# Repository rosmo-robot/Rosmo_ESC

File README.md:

# Rosmo ESC

Design for [Rosmo](https://rosmo.io) ESC - in M5Stack format.

[Schematic (PDF)](./Rosmo_ESC.pdf)

Top:

Bottom:

## Features

* Dual brushless motor ESC in M5-Stack module format
* Drives 2x 3-phase BLDC motors with up to 40V and 5A (cooling needed - to be tested)
* 2x SPI sensors supported, such as MA732, MA730, AS5048A, AS5047, etc...
* Control inputs via SPI, I2C    (and GPIO:question:)
* Grove port for I2C input/output

## Status

:warning: In development, prototype boards on order.

At the moment, schematic is complete and board has been routed. The BOM is complete but my have to change due to component availability.

**Do not use this for anything yet!**

## Pinout

Prototype pinout, based on STM32G491MET6, which is probably not the final MCU for this design, but a suitable (if maybe overpowered and therefore expensive) one that was available in the current semiconductor shortage. This MCU is 12x12mm LQFP-80, which is more than enough pins.

Functionality supported by this pinout:

* 2x 3-phase BLDC motor control with 6 PWM (6 outputs on TIM1 and 6 on TIM8, in CHx/CHxN configuration)
* 2x nSLEEP outputs (GPIO)
* 2x nFAULT inputs (interrupt GPIO)
* 2x 3-phase low-side current sensing (6 single-ended inputs on ADC1)
* 1x battery voltage monitor (1 single-ended input on ADC2)
* 3x SPI w/ hardware NSS pin (2 sensor ports + M5 stack SPI pins)
* 2x I2C (grove port + M5 stack SPI)
* USB FS connected to USB-C port (should allow serial monitor function and DFU firmware flashing)
* WAKE input (M5 GPIO connected to system wake 1, so M5 ESP32 can wake STM32 from sleep)
* SWD debug pins connected to standard ARM-10 debug header
* LED pin connected to status LED (or NeoPixel LED)
* BOOT0, nRST, OSC_IN - STM32 system pins

## Dependencies

The design uses various custom symbols and footprints. They should load from the project-internal cache when you open the project. If they do not, you can find [a kicad library](https://github.com/runger1101001/kicad-lib-runger) here which contains all the symbols/footprints used, among others.

Uses KiCad 6.

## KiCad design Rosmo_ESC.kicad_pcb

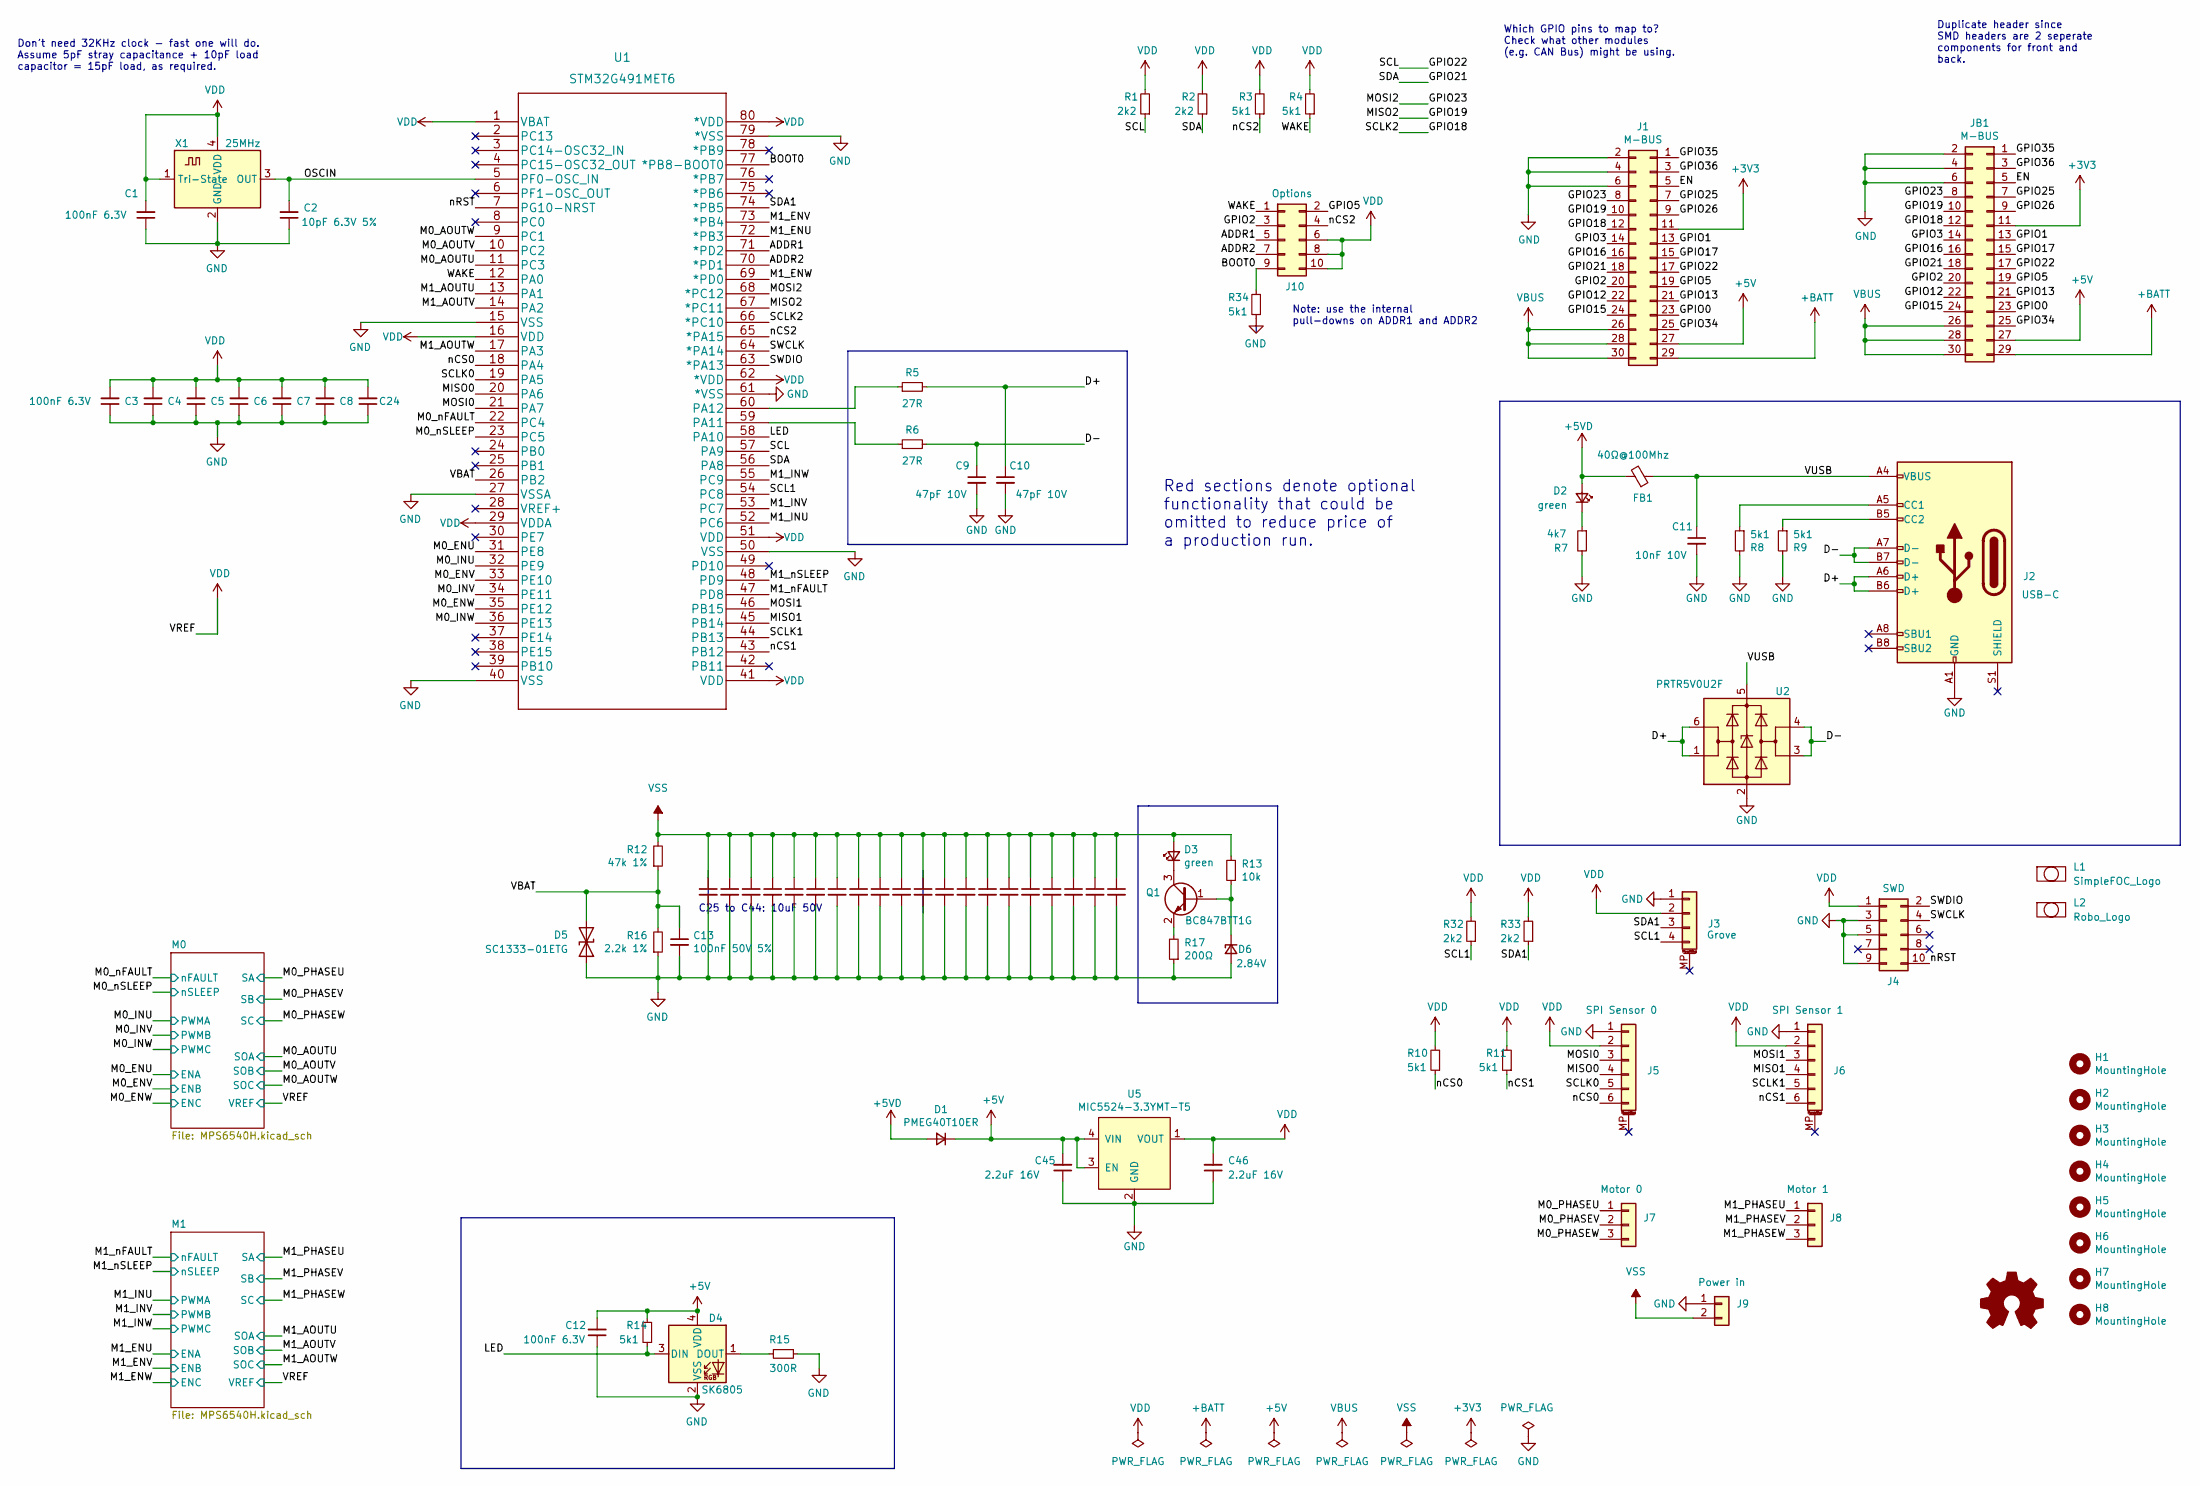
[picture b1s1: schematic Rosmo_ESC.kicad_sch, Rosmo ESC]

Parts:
C1, C3, C4, C5, C6, C7, C8, C12, C24: 100nF 6.3V; C_0402_1005Metric; Part CL05B104KQ5NNNC
C2: 10pF 6.3V 5%; C_0402_1005Metric; Part 04026A100JAT2A
C9, C10: 47pF 10V; C_0402_1005Metric; Part VJ0402A470GXQCW1BC
C11: 10nF 10V; C_0402_1005Metric; Part LMF105B7103KVHF
C13: 100nF 50V 5%; C_0402_1005Metric; Part GRM155C71H104JE19D
C25, C26, C27, C28, C29, C30, C31, C32, C33, C34, C35, C36, C37, C38, C39, C40, C41, C42, C43, C44: 10uF 50V; C_0805_2012Metric; Part GRM21BR61H106KE43L
C45, C46: 2.2uF 16V; C_0603_1608Metric; Part EMK107ABJ225KA8T
D1: PMEG40T10ER; D_SOD-123; Part PMEG40T10ER
D2, D3: green; LED_0402_1005Metric; Part 150040VS73240
D4: SK6805; LED_SK6805_PLCC4_2.4x2.7mm_P1.3mm; Part SK6805-2427
D5: SC1333-01ETG; D_0402_1005Metric; Part SC1333-01ETG
D6: 2.84V; D_SOD-523; Part CZRU52C2V7-HF
FB1: 40Ω@100Mhz; L_0805_2012Metric; Part MI0805K400R-10
H1, H2, H3, H4: MountingHole; BF@MountingHole_3.2mm_M3
H5, H6, H7, H8: MountingHole; BF@MountingHole_2.2mm_M2
J1: M-BUS; BF@M5Stack_MBUS; Part 89898-315BLF
J2: USB_C_Receptacle_USB2.0; USB_C_Receptacle_HRO_TYPE-C-31-M-12; Part HRO_TYPE-C-31-M-12
J3: Conn_01x04_MountingPin; Grove_A2006WF-04A; Part GR008WR-S-4P
J4, J10: Conn_02x05; PinHeader_2x05_P1.27mm_Vertical_SMD; Part 20021121-00010C8LF
J5, J6: JST_SH_SM06B-SRSS-TB_1x06-1MP; JST_SH_SM06B-SRSS-TB_1x06-1MP_P1.00mm_Horizontal; Part JST_SH_SM06B-SRSS-TB_1x06-1MP
J7, J8: Conn_01x03; TerminalBlock_Phoenix_PT-1,5-3-3.5-H_1x03_P3.50mm_Horizontal; Part 20020110-C034A01LF
J9: Conn_01x02; TerminalBlock_Phoenix_PT-1,5-2-3.5-H_1x02_P3.50mm_Horizontal; Part 20020110-C021A01LF
JB1: M-BUS; PinHeader_2x15_P2.54mm_Vertical_SMD; Part TSM-115-04-T-DV
L1: SimpleFOC_Logo; MadeForSimpleFOC_16mm
L2: Robo_Logo; Robo_logo2
L3: Logo_Open_Hardware_Small; OSHW-Symbol_6.7x6mm_SilkScreen
Q1: BC847BTT1G; SOT-416; Part BC847BTT1G
R1, R2, R32, R33: 2k2; R_0402_1005Metric
R3, R4, R8, R9, R10, R11, R14, R34: 5k1; R_0402_1005Metric
R5, R6: 27R; R_0402_1005Metric
R7: 4k7; R_0402_1005Metric
R12: 47k 1%; R_0402_1005Metric; Part CRCW040247K0FKEDC
R13: 10k; R_0402_1005Metric
R15: 300R; R_0402_1005Metric
R16: 2.2k 1%; R_0402_1005Metric; Part RT0402DRE072K2L
R17: 200Ω; R_0402_1005Metric
U1: STM32G491MET6; LQFP-80_12x12mm_P0.5mm; Part STM32G491MET6
U2: PRTR5V0U2F; SOT-886; Part PRTR5V0U2F
U5: MIC5524-3.3YMT-T5; TDFN-4-1EP_1x1mm_P0.65mm_EP0.5x0.5mm; Part MIC5524-3.3YMT-T5
X1: 25MHz; Oscillator_SMD_Abracon_ASCO-4Pin_1.6x1.2mm; Part ASCO-25.000MHZ-EK-T3

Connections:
+3V3: J1.11, JB1.11
+5V: C12.2, C45.2, D1.1 (K), D4.4 (VDD), J1.27, JB1.27, R14.2, U5.3 (EN), U5.4 (VIN)
+5VD: D1.2 (A), D2.2 (A), FB1.2
+BATT: J1.29, JB1.29
/ADDR1: J10.5, U1.71 (*PD2)
/ADDR2: J10.7, U1.70 (*PD1)
/BOOT0: J10.9, R34.2, U1.77 (*PB8-BOOT0)
/D+: C10.1, J2.A6 (D+), J2.B6 (D+), R5.2, U2.1 (I/O1), U2.6 (I/O1)
/D-: C9.1, J2.A7 (D-), J2.B7 (D-), R6.2, U2.3 (I/O2), U2.4 (I/O2)
/EN: J1.5, JB1.5
/GPIO0: J1.23, JB1.23
/GPIO1: J1.13, JB1.13
/GPIO2: J1.20, J10.3, JB1.20
/GPIO3: J1.14, JB1.14
/GPIO5: J1.19, J10.2, JB1.19
/GPIO12: J1.22, JB1.22
/GPIO13: J1.21, JB1.21
/GPIO15: J1.24, JB1.24
/GPIO16: J1.16, JB1.16
/GPIO17: J1.15, JB1.15
/GPIO18: J1.12, JB1.12, U1.66 (*PC10)
/GPIO19: J1.10, JB1.10, U1.67 (*PC11)
/GPIO21: J1.18, JB1.18, R2.1, U1.56 (PA8)
/GPIO22: J1.17, JB1.17, R1.1, U1.57 (PA9)
/GPIO23: J1.8, JB1.8, U1.68 (*PC12)
/GPIO25: J1.7, JB1.7
/GPIO26: J1.9, JB1.9
/GPIO34: J1.25, JB1.25
/GPIO35: J1.1, JB1.1
/GPIO36: J1.3, JB1.3
/LED: D4.3 (DIN), R14.1, U1.58 (PA10)
/M0_AOUTU: U1.11 (PC3); also elsewhere on the board
/M0_AOUTV: U1.10 (PC2); also elsewhere on the board
/M0_AOUTW: U1.9 (PC1); also elsewhere on the board
/M0_ENU: U1.31 (PE8); also elsewhere on the board
/M0_ENV: U1.33 (PE10); also elsewhere on the board
/M0_ENW: U1.35 (PE12); also elsewhere on the board
/M0_INU: U1.32 (PE9); also elsewhere on the board
/M0_INV: U1.34 (PE11); also elsewhere on the board
/M0_INW: U1.36 (PE13); also elsewhere on the board
/M0_PHASEU: J7.1; also elsewhere on the board
/M0_PHASEV: J7.2; also elsewhere on the board
/M0_PHASEW: J7.3; also elsewhere on the board
/M0_nFAULT: U1.22 (PC4); also elsewhere on the board
/M0_nSLEEP: U1.23 (PC5); also elsewhere on the board
/M1_AOUTU: U1.13 (PA1); also elsewhere on the board
/M1_AOUTV: U1.14 (PA2); also elsewhere on the board
/M1_AOUTW: U1.17 (PA3); also elsewhere on the board
/M1_ENU: U1.72 (*PB3); also elsewhere on the board
/M1_ENV: U1.73 (*PB4); also elsewhere on the board
/M1_ENW: U1.69 (*PD0); also elsewhere on the board
/M1_INU: U1.52 (PC6); also elsewhere on the board
/M1_INV: U1.53 (PC7); also elsewhere on the board
/M1_INW: U1.55 (PC9); also elsewhere on the board
/M1_PHASEU: J8.1; also elsewhere on the board
/M1_PHASEV: J8.2; also elsewhere on the board
/M1_PHASEW: J8.3; also elsewhere on the board
/M1_nFAULT: U1.47 (PD8); also elsewhere on the board
/M1_nSLEEP: U1.48 (PD9); also elsewhere on the board
/MISO0: J5.4, U1.20 (PA6)
/MISO1: J6.4, U1.45 (PB14)
/MOSI0: J5.3, U1.21 (PA7)
/MOSI1: J6.3, U1.46 (PB15)
/OSCIN: C2.2, U1.5 (PF0-OSC_IN), X1.3 (OUT)
/SCL1: J3.4, R32.1, U1.54 (PC8)
/SCLK0: J5.5, U1.19 (PA5)
/SCLK1: J6.5, U1.44 (PB13)
/SDA1: J3.3, R33.1, U1.74 (*PB5)
/SWCLK: J4.4, U1.64 (*PA14)
/SWDIO: J4.2, U1.63 (*PA13)
/VBAT: C13.1, D5.2 (A2), R12.1, R16.2, U1.26 (PB2)
/VUSB: C11.1, FB1.1, J2.A4 (VBUS), J2.A9 (VBUS), J2.B4 (VBUS), J2.B9 (VBUS), U2.5 (VBUS)
/WAKE: J10.1, R4.1, U1.12 (PA0)
/nCS0: J5.6, R10.1, U1.18 (PA4)
/nCS1: J6.6, R11.1, U1.43 (PB12)
/nCS2: J10.4, R3.1, U1.65 (*PA15)
/nRST: J4.10, U1.7 (PG10-NRST)
GND: C1.1, C2.1, C3.1, C4.1, C5.1, C6.1, C7.1, C8.1, C9.2, C10.2, C11.2, C12.1, C13.2, C24.1, C25.2, C26.2, C27.2, C28.2, C29.2, C30.2, C31.2, C32.2, C33.2, C34.2, C35.2, C36.2, C37.2, C38.2, C39.2, C40.2, C41.2, C42.2, C43.2, C44.2, C45.1, C46.1, D4.2 (VSS), D5.1 (A1), D6.2 (A), J1.2, J1.4, J1.6, J2.A1 (GND), J2.A12 (GND), J2.B1 (GND), J2.B12 (GND), J3.1, J4.3, J4.5, J4.9, J5.1, J6.1, J9.1, JB1.2, JB1.4, JB1.6, R7.2, R8.2, R9.2, R15.1, R16.1, R17.1, R34.1, U1.15 (VSS), U1.27 (VSSA), U1.40 (VSS), U1.50 (VSS), U1.61 (*VSS), U1.79 (*VSS), U2.2 (GND), U5.2 (GND), U5.5 (GND), X1.2 (GND); also elsewhere on the board
unnamed: D2.1 (K), R7.1
unnamed: D3.1 (K), Q1.3 (C)
unnamed: D4.1 (DOUT), R15.2
unnamed: D6.1 (K), Q1.1 (B), R13.1
unnamed: J2.A5 (CC1), R8.1
unnamed: J2.B5 (CC2), R9.1
unnamed: Q1.2 (E), R17.2
unnamed: R5.1, U1.60 (PA12)
unnamed: R6.1, U1.59 (PA11)
VBUS: J1.26, J1.28, J1.30, JB1.26, JB1.28, JB1.30
VDD: C1.2, C3.2, C4.2, C5.2, C6.2, C7.2, C8.2, C24.2, C46.2, J3.2, J4.1, J5.2, J6.2, J10.6, J10.8, J10.10, R1.2, R2.2, R3.2, R4.2, R10.2, R11.2, R32.2, R33.2, U1.1 (VBAT), U1.16 (VDD), U1.29 (VDDA), U1.41 (VDD), U1.51 (VDD), U1.62 (*VDD), U1.80 (*VDD), U5.1 (VOUT), X1.1 (Tri-State), X1.4 (VDD); also elsewhere on the board
VSS: C25.1, C26.1, C27.1, C28.1, C29.1, C30.1, C31.1, C32.1, C33.1, C34.1, C35.1, C36.1, C37.1, C38.1, C39.1, C40.1, C41.1, C42.1, C43.1, C44.1, D3.2 (A), J9.2, R12.2, R13.2; also elsewhere on the board

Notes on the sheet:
Which GPIO pins to map to? Check what other modules (e.g. CAN Bus) might be using.
C25 to C44: 10uF 50V
Don’t need 32KHz clock - fast one will do. Assume 5pF stray capacitance + 10pF load capacitor = 15pF load, as required.
Duplicate header since SMD headers are 2 seperate components for front and back.
Red sections denote optional functionality that could be omitted to reduce price of a production run.
Note: use the internal pull-downs on ADDR1 and ADDR2

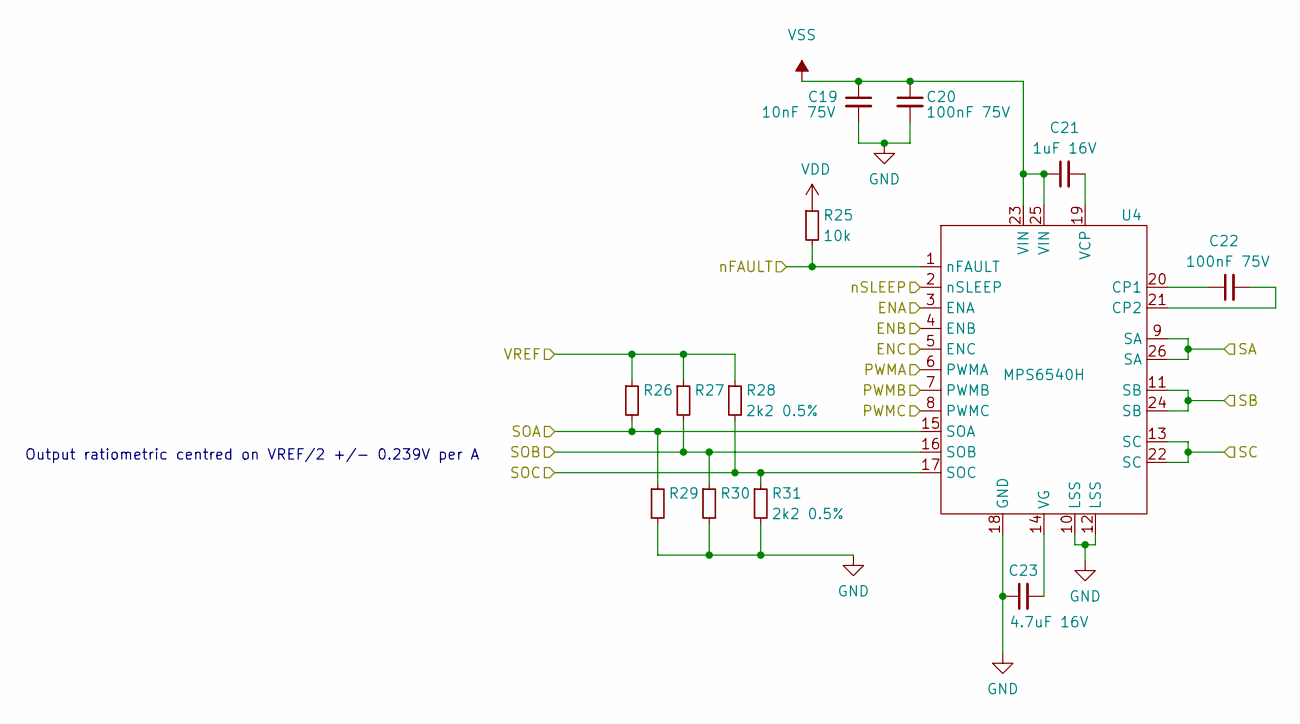
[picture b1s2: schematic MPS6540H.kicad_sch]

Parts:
C19: 10nF 75V; C_0805_2012Metric; Part GRM21BR72A103KA01K
C20, C22: 100nF 75V; C_0805_2012Metric; Part GCM21BR72A104KA37L
C21: 1uF 16V; C_0603_1608Metric; Part GCM188R71C105KA64J
C23: 4.7uF 16V; C_0603_1608Metric; Part GRT188C71C475KE13D
R25: 10k; R_0402_1005Metric
R26, R27, R28, R29, R30, R31: 2k2 0.5%; R_0402_1005Metric; Part RT0402DRE072K2L
U4: MPS6540H; Part MPS6540H

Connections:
/M1_AOUTU: R26.2, R29.1, U4.15 (SOA); also elsewhere on the board
/M1_AOUTV: R27.2, R30.1, U4.16 (SOB); also elsewhere on the board
/M1_AOUTW: R28.2, R31.1, U4.17 (SOC); also elsewhere on the board
/M1_ENU: U4.3 (ENA); also elsewhere on the board
/M1_ENV: U4.4 (ENB); also elsewhere on the board
/M1_ENW: U4.5 (ENC); also elsewhere on the board
/M1_INU: U4.6 (PWMA); also elsewhere on the board
/M1_INV: U4.7 (PWMB); also elsewhere on the board
/M1_INW: U4.8 (PWMC); also elsewhere on the board
/M1_PHASEU: U4.9 (SA), U4.26 (SA); also elsewhere on the board
/M1_PHASEV: U4.11 (SB), U4.24 (SB); also elsewhere on the board
/M1_PHASEW: U4.13 (SC), U4.22 (SC); also elsewhere on the board
/M1_nFAULT: R25.2, U4.1 (nFAULT); also elsewhere on the board
/M1_nSLEEP: U4.2 (nSLEEP); also elsewhere on the board
GND: C19.2, C20.2, C23.1, R29.2, R30.2, R31.2, U4.10 (LSS), U4.12 (LSS), U4.18 (GND); also elsewhere on the board
unnamed: C21.2, U4.19 (VCP)
unnamed: C22.1, U4.20 (CP1)
unnamed: C22.2, U4.21 (CP2)
unnamed: C23.2, U4.14 (VG)
VDD: R25.1, R26.1, R27.1, R28.1; also elsewhere on the board
VSS: C19.1, C20.1, C21.1, U4.23 (VIN), U4.25 (VIN); also elsewhere on the board

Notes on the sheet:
Output ratiometric centred on VREF/2 +/- 0.239V per A

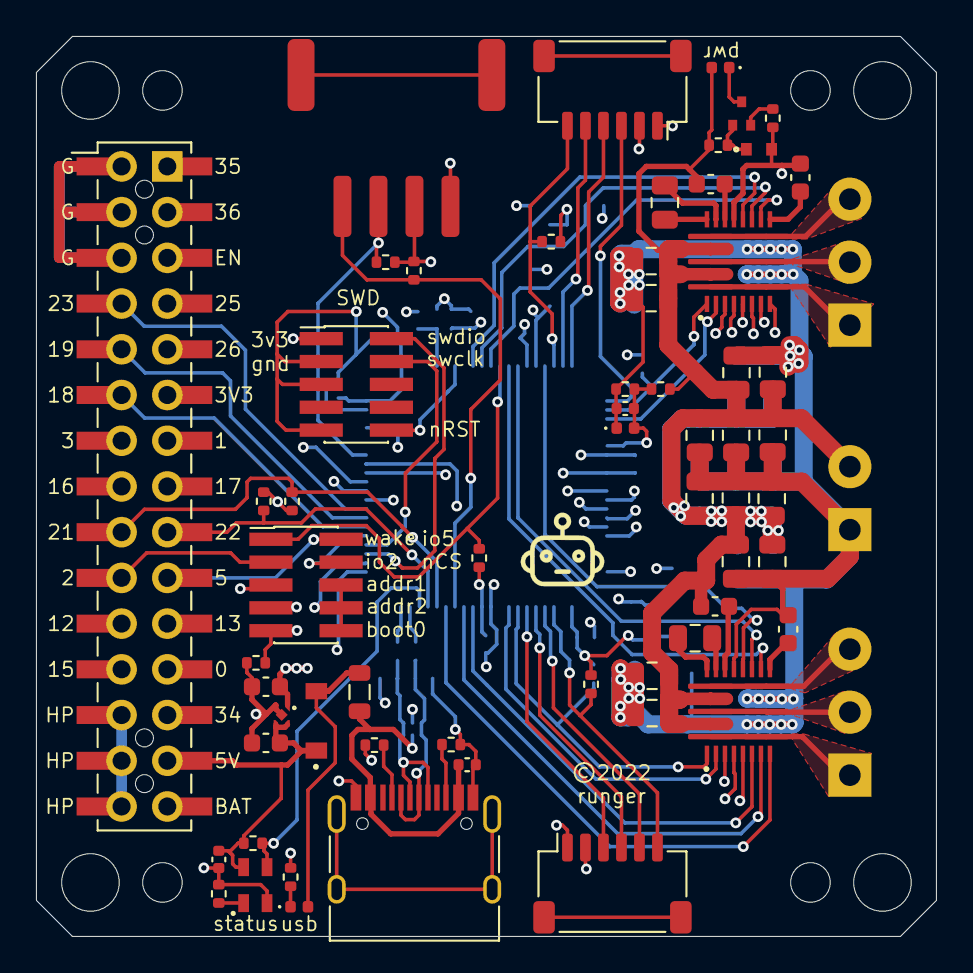
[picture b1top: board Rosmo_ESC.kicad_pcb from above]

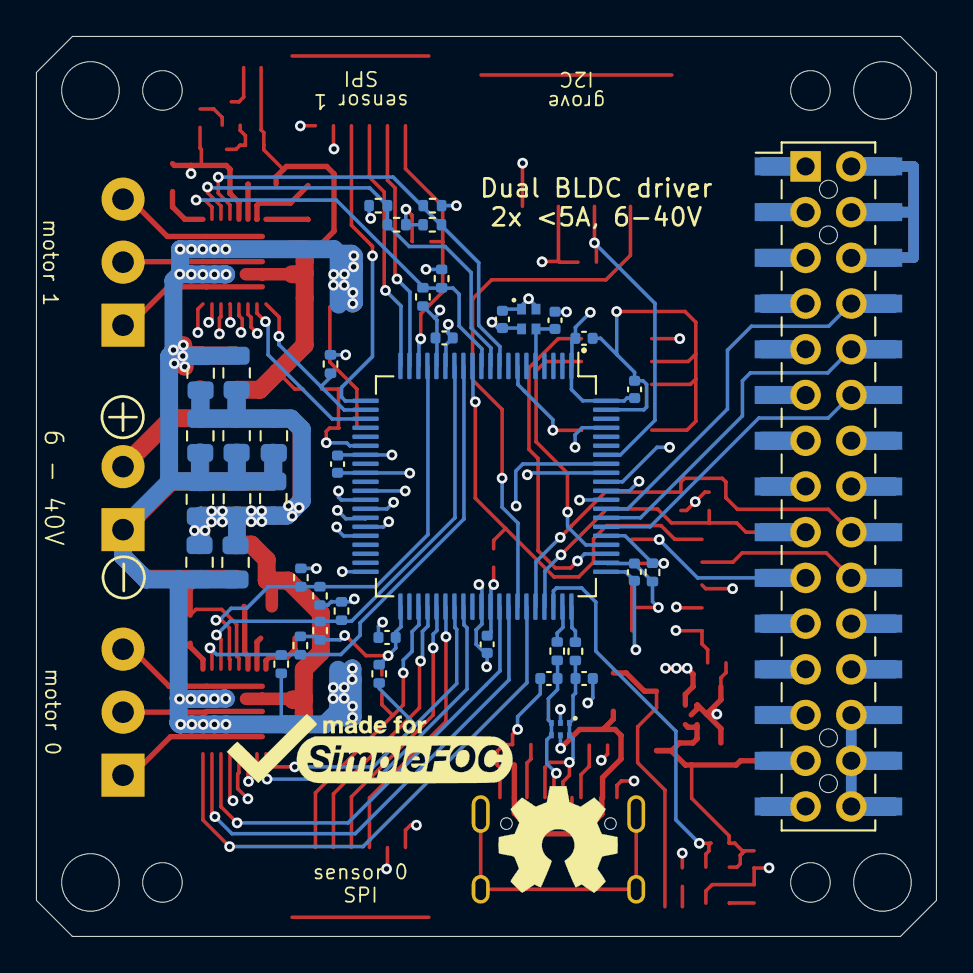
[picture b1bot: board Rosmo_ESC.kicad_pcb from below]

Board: 4 copper layers, 50.0 x 50.0 mm, 116 parts (44 on the bottom side), 98 nets.

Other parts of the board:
C14: 10nF 75V; C_0805_2012Metric
C15, C17: 100nF 75V; C_0805_2012Metric
C16: 1uF 16V; C_0603_1608Metric
C18: 4.7uF 16V; C_0603_1608Metric
R18: 10k; R_0402_1005Metric
R19, R20, R21, R22, R23, R24: 2k2 0.5%; R_0402_1005Metric
U3: MPS6540H

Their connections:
/M0_AOUTU: R19.2, R22.1, U3.15 (SOA); also elsewhere on the board
/M0_AOUTV: R20.2, R23.1, U3.16 (SOB); also elsewhere on the board
/M0_AOUTW: R21.2, R24.1, U3.17 (SOC); also elsewhere on the board
/M0_ENU: U3.3 (ENA); also elsewhere on the board
/M0_ENV: U3.4 (ENB); also elsewhere on the board
/M0_ENW: U3.5 (ENC); also elsewhere on the board
/M0_INU: U3.6 (PWMA); also elsewhere on the board
/M0_INV: U3.7 (PWMB); also elsewhere on the board
/M0_INW: U3.8 (PWMC); also elsewhere on the board
/M0_PHASEU: U3.9 (SA), U3.26 (SA); also elsewhere on the board
/M0_PHASEV: U3.11 (SB), U3.24 (SB); also elsewhere on the board
/M0_PHASEW: U3.13 (SC), U3.22 (SC); also elsewhere on the board
/M0_nFAULT: R18.2, U3.1 (nFAULT); also elsewhere on the board
/M0_nSLEEP: U3.2 (nSLEEP); also elsewhere on the board
GND: C14.2, C15.2, C18.1, R22.2, R23.2, R24.2, U3.10 (LSS), U3.12 (LSS), U3.18 (GND); also elsewhere on the board
unnamed: C16.2, U3.19 (VCP)
unnamed: C17.1, U3.20 (CP1)
unnamed: C17.2, U3.21 (CP2)
unnamed: C18.2, U3.14 (VG)
VDD: R18.1, R19.1, R20.1, R21.1; also elsewhere on the board
VSS: C14.1, C15.1, C16.1, U3.23 (VIN), U3.25 (VIN); also elsewhere on the board

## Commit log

2021-11-29 first commit, unfinished, just looking at dimensions
2021-11-29 added a readme
2021-11-29 fix image link
2021-12-14 working on rosmo ESC, routing half done
2021-12-14 added preliminary pinout diagramme
2021-12-14 fix README to new pinout
2021-12-14 updated README, added schematic PDF
2021-12-16 Update README.md
    Just added link to Rosmo doc
2021-12-17 intial routing done
2021-12-19 Added permissive CERN license
    https://ohwr.org/cern_ohl_p_v2.txt
    https://ohwr.org/project/cernohl
2022-01-03 updated to KiCad 6
2022-01-04 refer to KiCad 6 in README.
2022-01-09 v1 prototype for production
2022-01-10 Update README.md
    Website link rather than old document
2022-01-10 updated pinout diagramme

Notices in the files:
Rosmo_ESC.kicad_pcb:
©2022
